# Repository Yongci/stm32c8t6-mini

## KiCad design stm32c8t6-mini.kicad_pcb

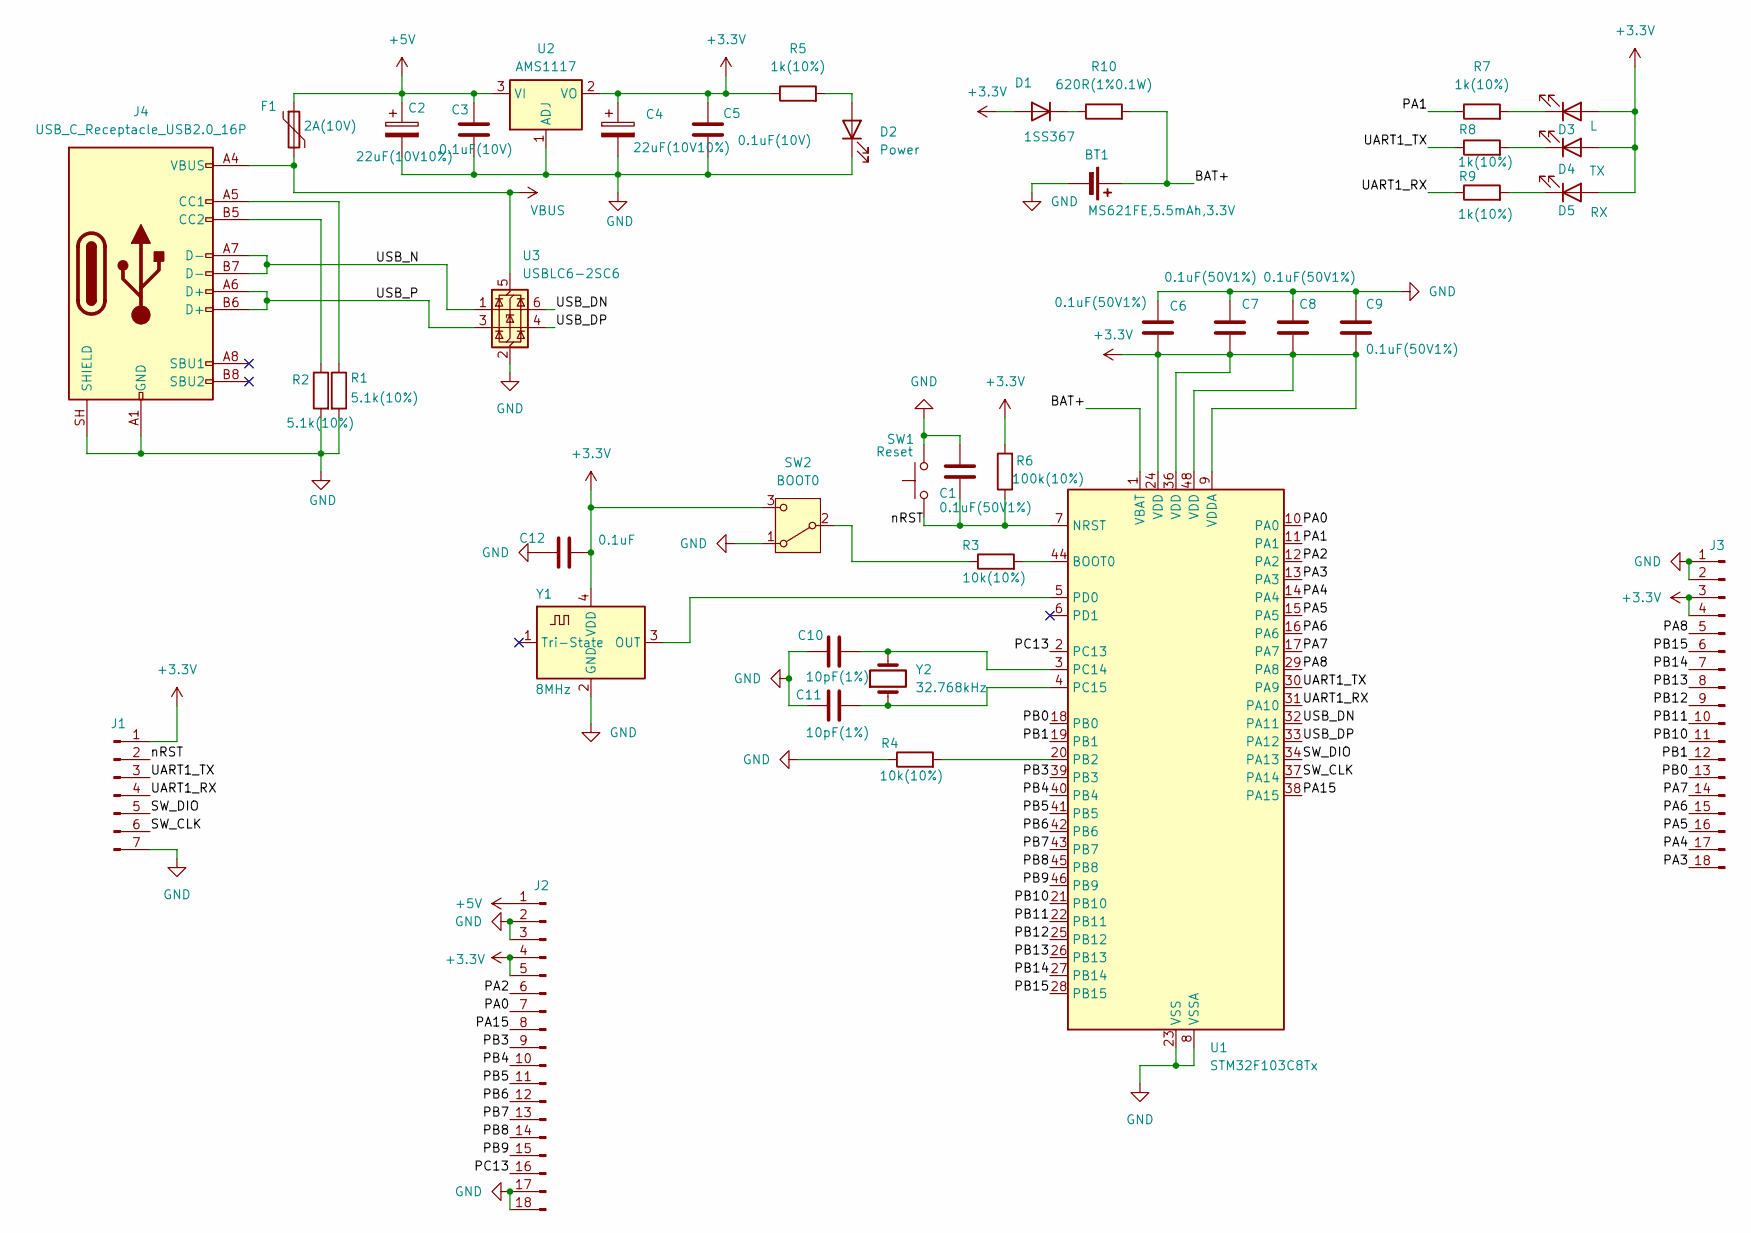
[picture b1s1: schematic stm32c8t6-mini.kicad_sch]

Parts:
BT1: MS621FE,5.5mAh,3.3V; BatteryHolder_Seiko_MS621F
C1, C6, C7, C8, C9: 0.1uF(50V1%); C_0402_1005Metric
C2, C4: 22uF(10V10%); CP_EIA-3216-10_Kemet-I
C3, C5: 0.1uF(10V); C_0402_1005Metric
C10, C11: 10pF(1%); C_0402_1005Metric
C12: 0.1uF; C_0402_1005Metric
D1: 1SS367; D_SOD-323
D2: Power; LED_0402_1005Metric
D3: L; LED_0402_1005Metric
D4: TX; LED_0402_1005Metric
D5: RX; LED_0402_1005Metric
F1: 2A(10V); Fuse_0805_2012Metric
J1: Conn_01x07_Pin; PinHeader_1x07_P2.54mm_Vertical
J2, J3: Conn_01x18_Pin; PinHeader_1x18_P2.54mm_Vertical
J4: USB_C_Receptacle_USB2.0_16P; USB_C_Receptacle_HRO_TYPE-C-31-M-12
R1, R2: 5.1k(10%); R_0402_1005Metric
R3, R4: 10k(10%); R_0402_1005Metric
R5, R7, R8, R9: 1k(10%); R_0402_1005Metric
R6: 100k(10%); R_0402_1005Metric
R10: 620R(1%0.1W); R_0603_1608Metric
SW1: Reset; SW_SPST_TS-1088-xR020
SW2: BOOT0; SW_DIP_SPSTx01_Slide_Copal_CVS-01xB_W5.9mm_P1mm
U1: STM32F103C8Tx; LQFP-48_7x7mm_P0.5mm
U2: AMS1117; SOT-223-3_TabPin2
U3: USBLC6-2SC6; SOT-23-6
Y1: 8MHz; Oscillator_SMD_Abracon_ASCO-4Pin_1.6x1.2mm
Y2: 32.768kHz; Crystal_SMD_3215-2Pin_3.2x1.5mm

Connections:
+3.3V: C4.1, C5.1, C6.2, C7.2, C8.2, C9.2, C12.2, D1.2 (A), D3.2 (A), D4.2 (A), D5.2 (A), J1.1, J2.4, J2.5, J3.3, J3.4, R5.1, R6.2, SW2.3 (C), U1.9 (VDDA), U1.24 (VDD), U1.36 (VDD), U1.48 (VDD), U2.2 (VO), Y1.4 (VDD)
+5V: C2.1, C3.1, F1.1, J2.1, U2.3 (VI)
/BAT+: BT1.1 (+), R10.2, U1.1 (VBAT)
/PA0: J2.7, U1.10 (PA0)
/PA1: R7.1, U1.11 (PA1)
/PA2: J2.6, U1.12 (PA2)
/PA3: J3.18, U1.13 (PA3)
/PA4: J3.17, U1.14 (PA4)
/PA5: J3.16, U1.15 (PA5)
/PA6: J3.15, U1.16 (PA6)
/PA7: J3.14, U1.17 (PA7)
/PA8: J3.5, U1.29 (PA8)
/PA15: J2.8, U1.38 (PA15)
/PB0: J3.13, U1.18 (PB0)
/PB1: J3.12, U1.19 (PB1)
/PB3: J2.9, U1.39 (PB3)
/PB4: J2.10, U1.40 (PB4)
/PB5: J2.11, U1.41 (PB5)
/PB6: J2.12, U1.42 (PB6)
/PB7: J2.13, U1.43 (PB7)
/PB8: J2.14, U1.45 (PB8)
/PB9: J2.15, U1.46 (PB9)
/PB10: J3.11, U1.21 (PB10)
/PB11: J3.10, U1.22 (PB11)
/PB12: J3.9, U1.25 (PB12)
/PB13: J3.8, U1.26 (PB13)
/PB14: J3.7, U1.27 (PB14)
/PB15: J3.6, U1.28 (PB15)
/PC13: J2.16, U1.2 (PC13)
/SW_CLK: J1.6, U1.37 (PA14)
/SW_DIO: J1.5, U1.34 (PA13)
/UART1_RX: J1.4, R9.1, U1.31 (PA10)
/UART1_TX: J1.3, R8.1, U1.30 (PA9)
/USB_DN: U1.32 (PA11), U3.6 (I/O1)
/USB_DP: U1.33 (PA12), U3.4 (I/O2)
/USB_N: J4.A7 (D-), J4.B7 (D-), U3.1 (I/O1)
/USB_P: J4.A6 (D+), J4.B6 (D+), U3.3 (I/O2)
/nRST: C1.2, J1.2, R6.1, SW1.1, U1.7 (NRST)
GND: BT1.2 (-), C1.1, C2.2, C3.2, C4.2, C5.2, C6.1, C7.1, C8.1, C9.1, C10.1, C11.1, C12.1, D2.1 (K), J1.7, J2.2, J2.3, J2.17, J2.18, J3.1, J3.2, J4.A1 (GND), J4.A12 (GND), J4.B1 (GND), J4.B12 (GND), J4.SH (SHIELD), R1.2, R2.2, R4.1, SW1.2, SW2.1 (A), U1.8 (VSSA), U1.23 (VSS), U1.35 (VSS), U1.47 (VSS), U2.1 (ADJ), U3.2 (GND), Y1.2 (GND)
unnamed: D1.1 (K), R10.1
unnamed: D2.2 (A), R5.2
unnamed: D3.1 (K), R7.2
unnamed: D4.1 (K), R8.2
unnamed: D5.1 (K), R9.2
unnamed: J4.A5 (CC1), R1.1
unnamed: J4.B5 (CC2), R2.1
unnamed: R3.1, SW2.2 (B)
unnamed: R3.2, U1.44 (BOOT0)
unnamed: R4.2, U1.20 (PB2)
unnamed: C10.2, U1.3 (PC14), Y2.2
unnamed: C11.2, U1.4 (PC15), Y2.1
unnamed: U1.5 (PD0), Y1.3 (OUT)
VBUS: F1.2, J4.A4 (VBUS), J4.A9 (VBUS), J4.B4 (VBUS), J4.B9 (VBUS), U3.5 (VBUS)

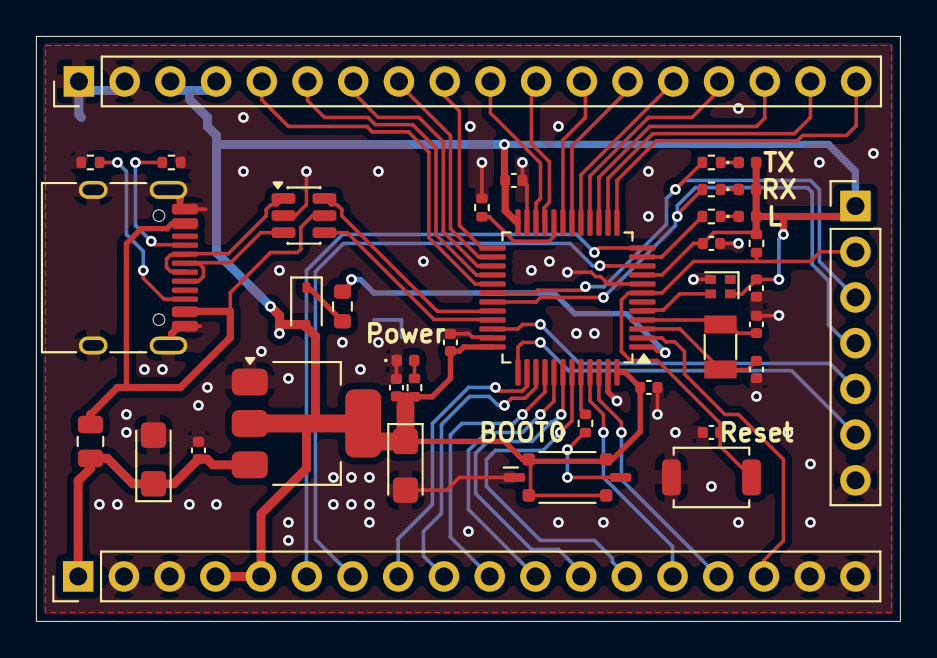
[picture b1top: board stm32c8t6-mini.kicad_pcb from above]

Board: 2 copper layers, 48.0 x 32.5 mm, 40 parts (1 on the bottom side), 53 nets.
